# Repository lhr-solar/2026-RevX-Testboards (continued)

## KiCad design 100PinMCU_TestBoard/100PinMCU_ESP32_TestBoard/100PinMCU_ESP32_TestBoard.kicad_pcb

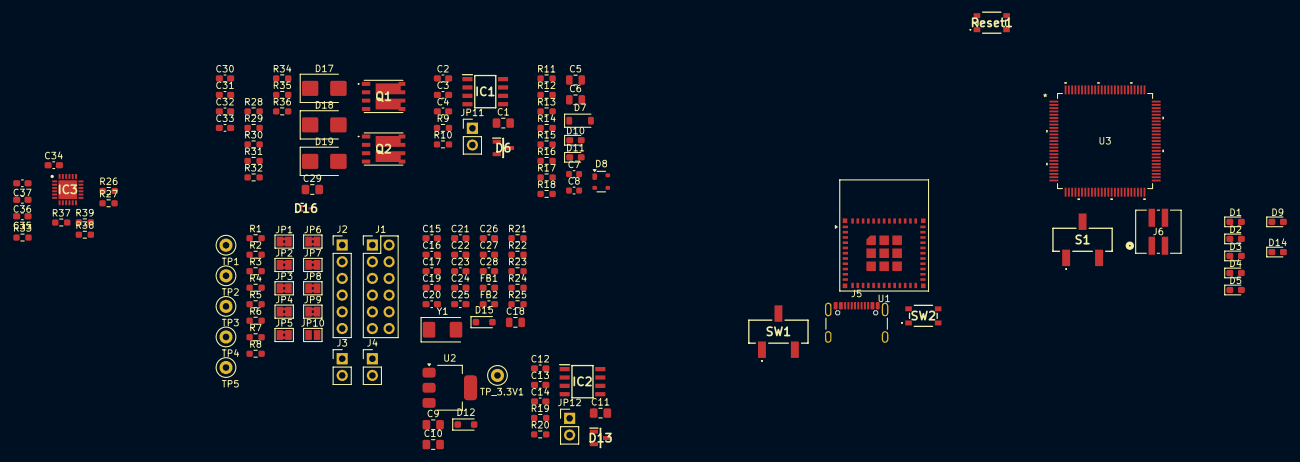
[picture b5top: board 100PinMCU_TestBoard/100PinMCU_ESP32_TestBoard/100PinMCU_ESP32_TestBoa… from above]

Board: 2 copper layers, 134 parts (0 on the bottom side), 98 nets, no tracks yet.

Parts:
C1, C9, C10, C11: 10u; C_0805_2012Metric_Pad1.18x1.45mm_HandSolder
C2, C3, C4, C12, C13, C14: 0.1u; C_0603_1608Metric_Pad1.08x0.95mm_HandSolder
C5, C6, C18: 10uF; C_0805_2012Metric
C7, C8: 0.1uF; C_0603_1608Metric
C15, C16: 26p; C_0603_1608Metric_Pad1.08x0.95mm_HandSolder
C17, C19, C20, C21, C22, C24, C26, C27, C28, C36, C37: 0.1uF; C_0603_1608Metric_Pad1.08x0.95mm_HandSolder
C23, C25, C30, C31, C32, C33, C34, C35: 1uF; C_0603_1608Metric_Pad1.08x0.95mm_HandSolder
C29: 10uF; C_0805_2012Metric_Pad1.18x1.45mm_HandSolder
D1, D2, D3, D4, D5, D14: LED; D_0603_1608Metric_Pad1.05x0.95mm_HandSolder
D6, D13: CDSOT23-T24CAN
D7: 1N5819HW-7-F; D_SOD-123
D8: SP0503BAHT; SOT-143
D9: ESP_PWR; D_0603_1608Metric_Pad1.05x0.95mm_HandSolder
D10: ESP_LED1; D_0603_1608Metric_Pad1.05x0.95mm_HandSolder
D11: ESP_LED2; D_0603_1608Metric_Pad1.05x0.95mm_HandSolder
D12: SBA130CH-AU_R1_000A1; D_SOD-323_HandSoldering
D15: D_TVS; D_SOD-323_HandSoldering
D16: TPD2EUSB30DRTR
D17: SMBJ24A-E3_52; D_SMB
D18, D19: SMBJ10A-E3_52; D_SMB
FB1, FB2: FerriteBead; L_0603_1608Metric_Pad1.05x0.95mm_HandSolder
IC1, IC2: TCAN3413DR
IC3: CYPD3177-24LQXQ
J1: Conn_02x06_Odd_Even; PinHeader_2x06_P2.54mm_Vertical
J2: Conn_01x06; PinHeader_1x06_P2.54mm_Vertical
J3, J4: Conn_01x02; PinHeader_1x02_P2.54mm_Vertical
J5: USB_C_Receptacle_USB2.0_16P; USB_C_Receptacle_GCT_USB4105-xx-A_16P_TopMnt_Horizontal
J6: SWD_Header_02x02; CONN04_878320406_MOL
JP1, JP2, JP3, JP4, JP5, JP6, JP7, JP8, JP9: Jumper_2_Bridged; SolderJumper-2_P1.3mm_Bridged2Bar_Pad1.0x1.5mm
JP10: Jumper_2_Open; SolderJumper-2_P1.3mm_Open_Pad1.0x1.5mm
JP11, JP12: TRM; PinHeader_1x02_P2.54mm_Vertical
Q1, Q2: SI7997DP-T1-GE3
R1, R2, R3, R4, R7, R8, R16, R17, R18, R25, R28, R29, R34: 1k; R_0603_1608Metric_Pad0.98x0.95mm_HandSolder
R5, R6, R37: 4.7k; R_0603_1608Metric_Pad0.98x0.95mm_HandSolder
R9, R10, R19, R20: 60; R_0603_1608Metric_Pad0.98x0.95mm_HandSolder
R11, R12, R26, R27, R32, R33, R35: 5.1k; R_0603_1608Metric_Pad0.98x0.95mm_HandSolder
R13, R14, R15, R23, R24, R30: 10k; R_0603_1608Metric_Pad0.98x0.95mm_HandSolder
R21, R22: 22; R_0603_1608Metric_Pad0.98x0.95mm_HandSolder
R31, R36: 49.9k; R_0603_1608Metric_Pad0.98x0.95mm_HandSolder
R38, R39: 2.2k; R_0603_1608Metric_Pad0.98x0.95mm_HandSolder
Reset1: Reset; TL3365AF180QG
S1: 450406020024
SW1: BOOT Switch; 450406020024
SW2: RESET Button; TL3365AF180QG
TP1, TP2, TP3, TP4, TP5: TestPoint; TestPoint_Loop_D1.80mm_Drill1.0mm_Beaded
TP_3.3V1: 3.3V; TestPoint_Loop_D1.80mm_Drill1.0mm_Beaded
U1: ESP32-C6-MINI-1
U2: MCP1826S; SOT-223-3_TabPin2
U3: STM32G491VET6; LQFP_491VET6_STM
Y1: Crystal; Crystal_SMD_Abracon_ABM3-2Pin_5.0x3.2mm

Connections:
+3.3V: C1.1, C2.1, C3.1, C11.1, C12.1, C13.1, IC1.3 (VCC), IC1.5 (SHDNV_IO), IC2.3 (VCC), IC2.5 (SHDNV_IO), JP4.2 (B), JP9.1 (A), JP10.1 (A), R5.1, R6.2, R8.1, TP1.1, TP5.1
+3.3V_ESP: C6.1, C6.2, C7.1, C7.2, JP9.2 (B), R14.1, R15.2, R16.1, SW1.1 (A), U1.3 (3V3)
/100PinMCU/3V3: C18.1, C20.1, C22.1, C24.1, C26.1, C27.1, FB2.1, J6.1, JP4.1 (A), R23.2, S1.3 (C), U3.6 (VBAT), U3.24 (VDD), U3.49 (VDD), U3.64 (VDD), U3.75 (VDD), U3.100 (VDD)
/100PinMCU/BOOT: JP1.1 (A), R24.1, U3.95 (PB8-BOOT0)
/100PinMCU/GNDA: C19.2, C21.2, C23.2, C25.2, C28.2, FB1.2, J2.6, U3.35 (VSSA)
/100PinMCU/PA9: JP6.1 (A), U3.70 (PA9)
/100PinMCU/PA10: JP7.1 (A), U3.71 (PA10)
/100PinMCU/PB12: IC2.4 (RXD), U3.51 (PB12)
/100PinMCU/PB13: IC2.1 (TXD), U3.52 (PB13)
/100PinMCU/PC0: JP2.1 (A), U3.15 (PC0)
/100PinMCU/PC1: JP3.1 (A), U3.16 (PC1)
/100PinMCU/PD2: JP5.1 (A), U3.84 (PD2)
/100PinMCU/PE8: R1.1, U3.39 (PE8)
/100PinMCU/PE11: R2.1, U3.42 (PE11)
/100PinMCU/PE12: R3.1, U3.43 (PE12)
/100PinMCU/PE14: R4.1, U3.45 (PE14)
/100PinMCU/PG10-NRST: C17.1, JP8.1 (A), R23.1, Reset1.1, U3.14 (PG10-NRST)
/100PinMCU/SWCLK: R21.1, U3.77 (PA14)
/100PinMCU/SWDIO: R22.1, U3.76 (PA13)
/100PinMCU/USB_DM: D16.2 (D-), U3.72 (PA11)
/100PinMCU/USB_DP: D16.1 (D+), U3.73 (PA12)
/100PinMCU/VDDA: C19.1, C21.1, C23.1, C25.1, C28.1, FB2.2, J2.1, U3.36 (VREF+), U3.37 (VDDA)
/ADC3_IN1: J2.2, U3.33 (PB1)
/ADC3_IN2: J2.3, U3.40 (PE9)
/ADC3_IN3: J2.4, U3.44 (PE13)
/ADC3_IN4: J2.5, U3.38 (PE7)
/CAN_Transceiver1/CAN_H: D13.1 (CAN_H), IC2.7 (CANH), J4.1, R19.1
/CAN_Transceiver1/CAN_L: D13.2 (CAN_L), IC2.6 (CANL), J4.2, JP12.2 (B)
/CAN_Transceiver/CAN_H: D6.1 (CAN_H), IC1.7 (CANH), J3.1, R9.1
/CAN_Transceiver/CAN_L: D6.2 (CAN_L), IC1.6 (CANL), J3.2, JP11.2 (B)
/ESP32/+5V_LDO_IN: C5.1, C33.1, D7.1 (K), D12.2 (A), Q2.5 (D2), Q2.6 (D2), Q2.10 (D2), Q2.12 (D2)
/ESP32/BOOT: R13.1, U1.23 (GPIO9)
/ESP32/ESP_GPIO1: JP8.2 (B), U1.19 (GPIO14)
/ESP32/ESP_GPIO2: JP1.2 (B), U1.20 (GPIO15)
/ESP32/ESP_GPIO3: JP2.2 (B), U1.24 (GPIO18)
/ESP32/ESP_GPIO4: JP3.2 (B), U1.25 (GPIO19)
/ESP32/ESP_RESET: C8.1, R7.2, R14.2, SW2.1, U1.8 (EN/CHIP_PU)
/ESP32/ESP_UART_RX: JP7.2 (B), TP3.1, U1.31 (U0TXD/GPIO16)
/ESP32/ESP_UART_TX: JP6.2 (B), TP2.1, U1.30 (U0RXD/GPIO17)
/ESP32/LED1: R17.1, U1.26 (GPIO20)
/ESP32/LED2: R18.1, U1.27 (GPIO21)
/ESP32/USB_D+: D8.2 (K), J5.A6 (D+), J5.B6 (D+), U1.18 (GPIO13/USB_D+)
/ESP32/USB_D-: D8.3 (K), J5.A7 (D-), J5.B7 (D-), U1.17 (GPIO12/USB_D-)
/ESP32/VBUSB: D7.2 (A), D8.4 (K), J5.A4 (VBUS), J5.A9 (VBUS), J5.B4 (VBUS), J5.B9 (VBUS)
/FDCAN1_RX: IC1.4 (RXD), J1.6, U3.82 (PD0)
/FDCAN1_TX: IC1.1 (TXD), J1.5, U3.83 (PD1)
/GPIO1: J1.11, U3.31 (PC5)
/I2C2_SCL: J1.2, R6.1, U3.30 (PC4)
/I2C2_SDA: J1.1, R5.2, U3.69 (PA8)
/LDO/Vout: C10.2, JP10.2 (B), TP_3.3V1.1, U2.3 (VO)
/SPI1_MISO: J1.8, U3.28 (PA6)
/SPI1_MOSI: J1.7, U3.29 (PA7)
/SPI1_NSS: J1.10, U3.26 (PA4)
/SPI1_SCK: J1.9, U3.27 (PA5)
/UART_RX: J1.4, U3.80 (PC11)
/UART_TX: J1.3, U3.79 (PC10)
/USB_PD/CC1: IC3.15 (CC1), R26.1
/USB_PD/CC2: IC3.14 (CC2), R27.1
/USB_PD/ISINK_COARSE: IC3.5 (ISNK_COARSE), R33.2, R35.1
/USB_PD/SAFE_PWR_EN: IC3.4 (SAFE_PWR_EN), R29.2
/USB_PD/SCL: IC3.13 (HPI_SCL), R38.2
/USB_PD/SDA: IC3.12 (HPI_SDA), R39.2
/USB_PD/VBUS_FET_EN: IC3.3 (VBUS_FET_EN), R28.2
/USB_PD/VBUS_MIN: IC3.1 (VBUS_MIN), R32.2, R34.1
/USB_PD/VDC_OUT: C32.1, IC3.11 (VDC_OUT), Q1.5 (D2), Q1.6 (D2), Q1.10 (D2), Q1.12 (D2)
GND: C1.2, C2.2, C3.2, C4.1, C5.2, C8.2, C9.1, C10.1, C11.2, C12.2, C13.2, C14.1, C15.1, C16.1, C17.2, C18.2, C20.2, C22.2, C24.2, C26.2, C27.2, C29.2, C34.1, C35.2, C36.2, C37.2, D1.1 (K), D2.1 (K), D3.1 (K), D4.1 (K), D5.1 (K), D6.3 (GND), D8.1 (A), D9.1 (K), D10.1 (K), D11.1 (K), D13.3 (GND), D15.1 (A1), D16.3 (GND), D17.2 (A), FB1.1, IC1.2 (GND), IC1.8 (STB), IC2.2 (GND), IC2.8 (STB), IC3.6 (ISNK_FINE), IC3.19 (GND_1), IC3.22 (GND_2), IC3.25 (GND_3), J1.12, J5.A1 (GND), J5.A12 (GND), J5.B1 (GND), J5.B12 (GND), J5.S1 (SHIELD), J5.S2 (Shield), J5.S3 (Shield), J5.S4 (Shield), J6.2, R11.2, R12.2, R25.2, R26.2, R27.2, R34.2, R35.2, Reset1.2, S1.1 (A), SW1.3 (C), SW2.2, TP4.1, U1.1 (GND), U1.2 (GND), U1.11 (GND), U1.14 (GND), U1.36 (GND), U1.37 (GND), U1.38 (GND), U1.39 (GND), U1.40 (GND), U1.41 (GND), U1.42 (GND), U1.43 (GND), U1.44 (GND), U1.45 (GND), U1.46 (GND), U1.47 (GND), U1.48 (GND), U1.49 (GND), U1.50 (GND), U1.51 (GND), U1.52 (GND), U1.53 (GND), U2.2 (GND), U3.23 (VSS), U3.48 (VSS), U3.63 (VSS), U3.74 (VSS), U3.99 (VSS)
unnamed: C4.2, R9.2, R10.1
unnamed: C14.2, R19.2, R20.1
unnamed: D1.2 (A), R1.2
unnamed: D2.2 (A), R2.2
unnamed: D3.2 (A), R3.2
unnamed: D4.2 (A), R4.2
unnamed: D5.2 (A), R8.2
unnamed: D9.2 (A), R16.2
unnamed: D10.2 (A), R17.2
unnamed: D11.2 (A), R18.2
unnamed: C9.2, D12.1 (K), U2.1 (VI)
unnamed: D14.2 (A), D15.2 (A2), R24.2, S1.2 (B)
unnamed: D14.1 (K), R25.1
unnamed: C31.2, C33.2, D18.2 (A), Q2.2 (G1), Q2.4 (G2), R29.1, R31.1
unnamed: D18.1 (K), Q2.1 (S1), Q2.3 (S2)
unnamed: C30.2, C32.2, D19.2 (A), Q1.2 (G1), Q1.4 (G2), R28.1, R30.1, R36.1
unnamed: D19.1 (K), Q1.1 (S1), Q1.3 (S2), R36.2
unnamed: IC3.10 (FLIP), R37.2
unnamed: C34.2, IC3.24 (VCCD)
unnamed: J5.A5 (CC1), R11.1
unnamed: J5.B5 (CC2), R12.1
unnamed: J6.3, R21.2
unnamed: J6.4, R22.2
unnamed: JP5.2 (B), R7.1
unnamed: JP11.1 (A), R10.2
unnamed: JP12.1 (A), R20.2
unnamed: R13.2, SW1.2 (B)
unnamed: R15.1, U1.22 (GPIO8)
unnamed: C16.2, U3.12 (PF0-OSC_IN), Y1.2
unnamed: C15.2, U3.13 (PF1-OSC_OUT), Y1.1
PD_3V3: C35.1, C36.1, C37.1, IC3.2 (VBUS_MAX), IC3.23 (VDDD), R32.1, R33.1, R37.1, R38.1, R39.1
VBUS_IN: C29.1, C30.1, C31.1, D17.1 (K), IC3.18 (VBUS_IN), Q1.7 (D1), Q1.8 (D1), Q1.9 (D1), Q1.11 (D1), Q2.7 (D1), Q2.8 (D1), Q2.9 (D1), Q2.11 (D1), R30.2, R31.2

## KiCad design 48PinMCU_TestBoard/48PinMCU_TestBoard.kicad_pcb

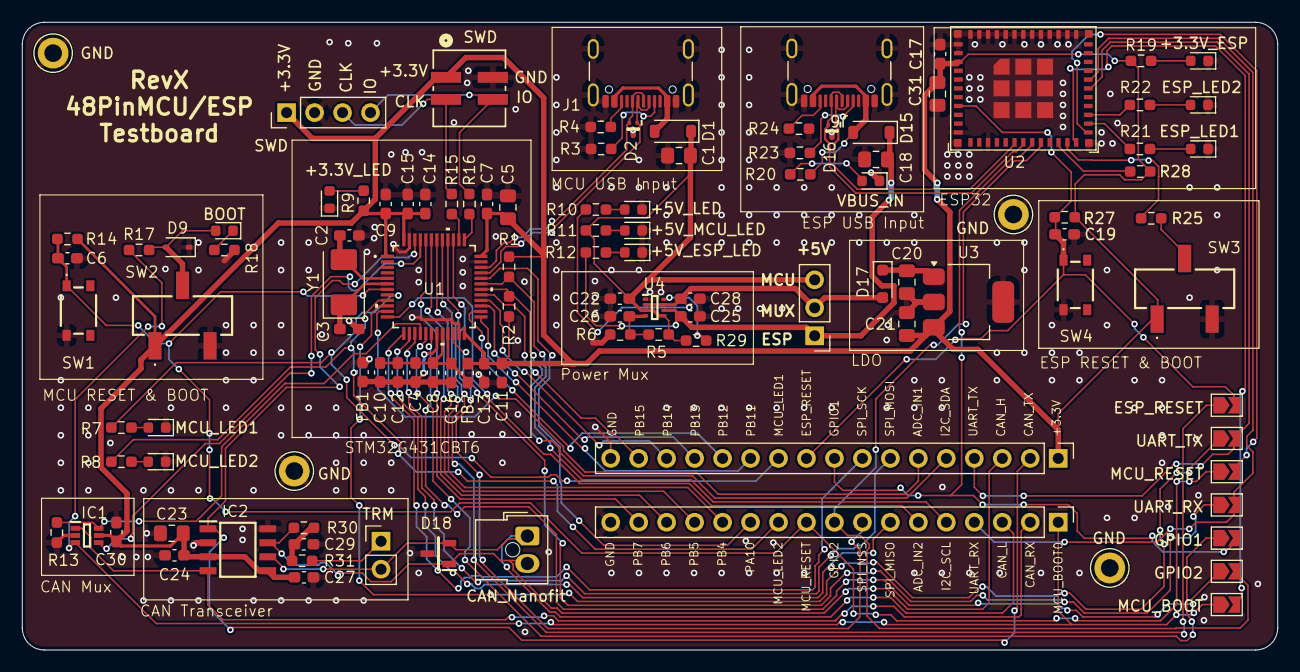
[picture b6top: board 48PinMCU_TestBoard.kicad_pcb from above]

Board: 2 copper layers, 114.0 x 57.0 mm, 112 parts (0 on the bottom side), 85 nets.

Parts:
C1, C5, C18, C31: 10uF; C_0805_2012Metric_Pad1.18x1.45mm_HandSolder
C2, C3: 26p; C_0603_1608Metric_Pad1.08x0.95mm_HandSolder
C4, C6, C7, C8, C9, C11, C13, C14, C15, C17, C19, C22, C25, C26, C28, C30: 0.1uF; C_0603_1608Metric_Pad1.08x0.95mm_HandSolder
C10, C12: 1uF; C_0603_1608Metric_Pad1.08x0.95mm_HandSolder
C16: 100nF; C_0603_1608Metric_Pad1.08x0.95mm_HandSolder
C20, C21, C23: 10u; C_0805_2012Metric_Pad1.18x1.45mm_HandSolder
C24, C27, C29: 0.1u; C_0603_1608Metric_Pad1.08x0.95mm_HandSolder
D1, D15: 1N5819HW-7-F; D_SOD-123
D2, D16: TPD2EUSB30DRTR
D3: MCU_LED1; D_0603_1608Metric
D4: MCU_LED2; D_0603_1608Metric
D5: +3.3V_LED; D_0603_1608Metric
D6: +5V_LED; D_0603_1608Metric
D7: +5V_MCU_LED; D_0603_1608Metric
D8: +5V_ESP_LED; D_0603_1608Metric
D9: D_TVS; D_SOD-323
D10: BOOT; D_0603_1608Metric
D11: +3.3V_ESP; D_0603_1608Metric
D12: VBUS_IN; D_0603_1608Metric
D13: ESP_LED1; D_0603_1608Metric
D14: ESP_LED2; D_0603_1608Metric
D17: SBA130CH-AU_R1_000A1; D_SOD-323_HandSoldering
D18: CDSOT23-T24CAN
FB1, FB2: FerriteBead; C_0603_1608Metric_Pad1.08x0.95mm_HandSolder
IC1: 74LVC1G157GW,125; SOP65P210X110-6N
IC2: TCAN3413DR
J1, J6: USB_C_Receptacle_USB2.0_16P; USB_C_Receptacle_GCT_USB4105-xx-A_16P_TopMnt_Horizontal
J2: CAN_Nanofit; Molex_Nano-Fit_105309-xx02_1x02_P2.50mm_Vertical
J3: Conn_01x03; PinHeader_1x03_P2.54mm_Vertical
J4: SWD; PinHeader_1x04_P2.54mm_Vertical
J5: SWD; CONN04_878320406_MOL
J7, J8: Conn_01x17; PinHeader_1x17_P2.54mm_Vertical
JP8: ESP_RESET; SolderJumper-2_P1.3mm_Open_TrianglePad1.0x1.5mm
JP9: UART_TX; SolderJumper-2_P1.3mm_Open_TrianglePad1.0x1.5mm
JP10: UART_RX; SolderJumper-2_P1.3mm_Open_TrianglePad1.0x1.5mm
JP11: GPIO1; SolderJumper-2_P1.3mm_Open_TrianglePad1.0x1.5mm
JP12: GPIO2; SolderJumper-2_P1.3mm_Open_TrianglePad1.0x1.5mm
JP13: MCU_BOOT; SolderJumper-2_P1.3mm_Open_TrianglePad1.0x1.5mm
JP14: MCU_RESET; SolderJumper-2_P1.3mm_Open_TrianglePad1.0x1.5mm
JP15: TRM; PinHeader_1x02_P2.54mm_Vertical
R1, R2, R13, R14, R17, R25, R27, R28, R29: 10k; R_0603_1608Metric_Pad0.98x0.95mm_HandSolder
R3, R4, R23, R24: 5.1k; R_0603_1608Metric_Pad0.98x0.95mm_HandSolder
R5: 16k; R_0603_1608Metric_Pad0.98x0.95mm_HandSolder
R6: 4.7k; R_0603_1608Metric_Pad0.98x0.95mm_HandSolder
R7, R8, R9, R18, R19, R21, R22: 1k; R_0603_1608Metric_Pad0.98x0.95mm_HandSolder
R10, R11, R12, R20: 2.2k; R_0603_1608Metric_Pad0.98x0.95mm_HandSolder
R15, R16: 22; R_0603_1608Metric_Pad0.98x0.95mm_HandSolder
R30, R31: 60; R_0603_1608Metric_Pad0.98x0.95mm_HandSolder
SW1: Reset; TL3365AF180QG
SW2: SW_SPDT; BootSW
SW3: BOOT Switch; BootSW
SW4: RESET Button; TL3365AF180QG
TP1, TP2, TP3, TP4: GND; TestPoint_Keystone_5005-5009_Compact
U1: STM32G431CBT6; 48PinMCU
U2: ESP32-C6-MINI-1
U3: MCP1826S; SOT-223-3_TabPin2
U4: TPS2117DRLR; SOTFL50P160X60-8N
Y1: Crystal; Crystal_SMD_Abracon_ABM3-2Pin_5.0x3.2mm

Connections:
+3.3V: C5.1, C7.1, C9.1, C11.1, C13.1, C14.1, C15.1, C17.1, C21.2, C23.1, C24.1, C27.1, C30.1, C31.1, FB2.1, IC1.5 (VCC), IC2.3 (VCC), IC2.5 (SHDNV_IO), J4.1, J5.1, J7.1, R1.1, R2.1, R9.1, R14.2, R19.1, R27.1, R28.2, SW2.1 (A), SW3.1 (A), U1.1 (VBAT), U1.24 (VDD), U1.36 (VDD), U1.48 (VDD), U2.3 (3V3), U3.3 (VO)
+5V: C28.1, D17.2 (A), J3.2, R10.1, U4.2 (VOUT), U4.7 (VOUT__1)
+5V_ESP: C18.1, C25.1, D15.1 (K), J3.1, R12.1, U4.6 (VIN2)
+5V_MCU: C1.1, C22.1, D1.1 (K), J3.3, R5.1, R11.1, R29.1, U4.3 (VIN1), U4.5 (MODE)
/ADC_IN_1: J7.6, U1.11 (PA3)
/ADC_IN_2: J8.6, U1.12 (PA4)
/CAN_H: D18.1 (CAN_H), IC2.7 (CANH), J2.2, J7.3, R30.1
/CAN_L: D18.2 (CAN_L), IC2.6 (CANL), J2.1, J8.3, JP15.2 (B)
/CAN_RX: IC1.1 (I1), IC2.4 (RXD), J8.2
/CAN_TX: IC2.1 (TXD), J7.2, U1.46 (PB9)
/ESP32/BOOT: R25.1, U2.23 (GPIO9)
/ESP32/LED1: R21.1, U2.26 (GPIO20)
/ESP32/LED2: R22.1, U2.27 (GPIO21)
/ESP32/USB_D+: D16.2 (D-), J6.A6 (D+), J6.B6 (D+), U2.18 (GPIO13/USB_D+)
/ESP32/USB_D-: D16.1 (D+), J6.A7 (D-), J6.B7 (D-), U2.17 (GPIO12/USB_D-)
/ESP32/VBUS: D15.2 (A), J6.A4 (VBUS), J6.A9 (VBUS), J6.B4 (VBUS), J6.B9 (VBUS), R20.1
/ESP_BREAKOUT1_E: J7.9, JP11.2 (B), U2.19 (GPIO14)
/ESP_BREAKOUT1_M: JP11.1 (A), U1.17 (PB1)
/ESP_BREAKOUT2_E: J8.9, JP12.2 (B), U2.20 (GPIO15)
/ESP_BREAKOUT2_M: JP12.1 (A), U1.18 (PB2)
/ESP_RESET_E: C19.1, J7.10, JP8.2 (B), R27.2, SW4.1, U2.8 (EN/CHIP_PU)
/ESP_RESET_M: JP8.1 (A), U1.40 (PB3)
/ESP_UART_RX_E: J8.4, JP10.2 (B), U2.31 (U0TXD/GPIO16)
/ESP_UART_RX_M: JP10.1 (A), U1.22 (PB10)
/ESP_UART_TX_E: J7.4, JP9.2 (B), U2.30 (U0RXD/GPIO17)
/ESP_UART_TX_M: JP9.1 (A), U1.10 (PA2)
/I2C_SCL: J8.5, R1.2, U1.31 (PA9)
/I2C_SDA: J7.5, R2.2, U1.30 (PA8)
/MCU/CAN_EN: IC1.6 (S), R13.2, U1.16 (PB0)
/MCU/CAN_RX/BOOT0: IC1.4 (Y), U1.45 (PB8-BOOT0)
/MCU/GNDA: C4.2, C8.2, C10.2, C12.2, C16.2, FB1.1, U1.19 (VSSA)
/MCU/SWCLK: R15.1, U1.38 (PA14)
/MCU/SWDIO: R16.1, U1.37 (PA13)
/MCU/VDDA: C4.1, C8.1, C10.1, C12.1, C16.1, FB2.2, U1.20 (VREF+), U1.21 (VDDA)
/MCU_BOOT0_E: JP13.2 (B), U2.24 (GPIO18)
/MCU_BOOT0_M: IC1.3 (I0), J8.1, JP13.1 (A), R17.1
/MCU_LED_1: J7.11, R7.1, U1.8 (PA0)
/MCU_LED_2: J8.11, R8.1, U1.9 (PA1)
/MCU_RESET_E: JP14.2 (B), U2.25 (GPIO19)
/MCU_RESET_M: C6.1, J8.10, JP14.1 (A), R14.1, SW1.1, U1.7 (PG10-NRST)
/PA10: J8.12, U1.32 (PA10)
/PB4: J8.13, U1.41 (PB4)
/PB5: J8.14, U1.42 (PB5)
/PB6: J8.15, U1.43 (PB6)
/PB7: J8.16, U1.44 (PB7)
/PB11: J7.12, U1.25 (PB11)
/PB12: J7.13, U1.26 (PB12)
/PB13: J7.14, U1.27 (PB13)
/PB14: J7.15, U1.28 (PB14)
/PB15: J7.16, U1.29 (PB15)
/Power Mux/PR1: C26.1, R5.2, R6.1, U4.4 (PR1)
/SPI_MISO: J8.7, U1.14 (PA6)
/SPI_MOSI: J7.7, U1.15 (PA7)
/SPI_NSS: J8.8, U1.39 (PA15)
/SPI_SCK: J7.8, U1.13 (PA5)
/USB_D+: D2.2 (D-), J1.A6 (D+), J1.B6 (D+), U1.34 (PA12)
/USB_D-: D2.1 (D+), J1.A7 (D-), J1.B7 (D-), U1.33 (PA11)
/VBUS: D1.2 (A), J1.A4 (VBUS), J1.A9 (VBUS), J1.B4 (VBUS), J1.B9 (VBUS)
GND: C1.2, C2.2, C3.1, C5.2, C6.2, C7.2, C9.2, C11.2, C13.2, C14.2, C15.2, C17.2, C18.2, C19.2, C20.1, C21.1, C22.2, C23.2, C24.2, C25.2, C26.2, C27.2, C28.2, C29.1, C30.2, C31.2, D2.3 (GND), D3.1 (K), D4.1 (K), D5.1 (K), D6.1 (K), D7.1 (K), D8.1 (K), D9.1 (A1), D11.1 (K), D12.1 (K), D13.1 (K), D14.1 (K), D16.3 (GND), D18.3 (GND), FB1.2, IC1.2 (GND), IC2.2 (GND), IC2.8 (STB), J1.A1 (GND), J1.A12 (GND), J1.B1 (GND), J1.B12 (GND), J1.S1 (SHIELD), J1.S2 (Shield), J1.S3 (Shield), J1.S4 (Shield), J4.2, J5.2, J6.A1 (GND), J6.A12 (GND), J6.B1 (GND), J6.B12 (GND), J6.S1 (SHIELD), J6.S2 (Shield), J6.S3 (Shield), J6.S4 (Shield), J7.17, J8.17, R3.2, R4.2, R6.2, R13.1, R18.2, R23.2, R24.2, SW1.2, SW2.3 (C), SW3.3 (C), SW4.2, TP1.1, TP2.1, TP3.1, TP4.1, U1.23 (VSS), U1.35 (VSS), U1.47 (VSS), U2.1 (GND), U2.2 (GND), U2.11 (GND), U2.14 (GND), U2.36 (GND), U2.37 (GND), U2.38 (GND), U2.39 (GND), U2.40 (GND), U2.41 (GND), U2.42 (GND), U2.43 (GND), U2.44 (GND), U2.45 (GND), U2.46 (GND), U2.47 (GND), U2.48 (GND), U2.49 (GND), U2.50 (GND), U2.51 (GND), U2.52 (GND), U2.53 (GND), U3.2 (GND), U4.1 (GND)
unnamed: C29.2, R30.2, R31.1
unnamed: D3.2 (A), R7.2
unnamed: D4.2 (A), R8.2
unnamed: D5.2 (A), R9.2
unnamed: D6.2 (A), R10.2
unnamed: D7.2 (A), R11.2
unnamed: D8.2 (A), R12.2
unnamed: D9.2 (A2), D10.2 (A), R17.2, SW2.2 (B)
unnamed: D10.1 (K), R18.1
unnamed: D11.2 (A), R19.2
unnamed: D12.2 (A), R20.2
unnamed: D13.2 (A), R21.2
unnamed: D14.2 (A), R22.2
unnamed: C20.2, D17.1 (K), U3.1 (VI)
unnamed: J1.A5 (CC1), R3.1
unnamed: J1.B5 (CC2), R4.1
unnamed: J4.3, J5.3, R15.2
unnamed: J4.4, J5.4, R16.2
unnamed: J6.A5 (CC1), R23.1
unnamed: J6.B5 (CC2), R24.1
unnamed: JP15.1 (A), R31.2
unnamed: R25.2, SW3.2 (B)
unnamed: C2.1, U1.5 (PF0-OSC_IN), Y1.2
unnamed: C3.2, U1.6 (PF1-OSC_OUT), Y1.1
unnamed: R28.1, U2.22 (GPIO8)
unnamed: R29.2, U4.8 (ST)

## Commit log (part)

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2026-05-11 started pd + boost testboard
2026-05-13 Add project link to README
2026-05-13 some stuff
2026-05-15 schematic
2026-05-15 init
2026-05-15 initial review
2026-05-15 init layout
2026-05-15 updated p/n
2026-05-18 addressed comments, changed PD block a little
2026-05-18 reviewed lakshay, ready for lil shah
2026-05-18 updated relative path for footprint/design path
2026-05-18 addressed all reviews, starting layout
2026-05-19 comments, load resistors, stuff idk
2026-05-19 esp32 design block will be updated later
2026-05-19 early layout stuff
2026-05-21 more layout
2026-05-21 cooking or no??
2026-05-21 something
2026-05-21 some tweaks
2026-05-21 footprints fixed
2026-05-21 footprints fixed actually
2026-05-22 fuse holder
2026-05-23 initial commit, schematic for testboard
2026-05-23 addressed final rounds of schematic comments, inital layouting
2026-05-24 made tony changes; broke out more pins
2026-05-28 lakshay comments addressed footprint p/n in progress
2026-05-28 comments
2026-05-28 addressed reviews
2026-05-29 1st iteration layout review
2026-05-29 pre japan flight
2026-05-29 pre board
2026-05-29 fixes made
2026-05-29 more fixes
2026-05-30 during flight
2026-05-30 clean up
2026-05-30 production files
2026-05-30 changed gitignore to push bom
2026-05-30 All fixes fixed
2026-05-30 preliminary layout blocks
2026-05-30 mount fuji tmrw
2026-05-30 addressed all final comments, review?
2026-05-31 Layout
2026-05-31 finished tony's review, should be good?
2026-05-31 added p/n for missing fields
2026-05-31 ready for lil shah
2026-05-31 added shorting jumpers
2026-06-01 added bypass caps in series with ESP DC input
2026-06-01 layout tweaks
2026-06-01 temp
2026-06-01 bump shpt
2026-06-01 made more changes!!
2026-06-01 gerbers
2026-06-01 add mux
2026-06-01 save before laptop dies
2026-06-01 more
2026-06-01 okay
2026-06-01 clark
2026-06-01 separate subcircuits
2026-06-01 can layout
2026-06-01 mcu layout
2026-06-01 all subcircuits layout
2026-06-01 updated with PP + gen gebers
2026-06-01 JLC gebers + minor silk fixes
2026-06-02 schem fixes + some semblance of layout ish
2026-06-02 more layout but me go sleep now
2026-06-03 she's an onion now
2026-06-03 initial layout (yes I will add funny silkscreen tmrw)
2026-06-03 oops my edge cuts were weird
2026-06-04 updated with new comments + new gen gebers
2026-06-05 ravi comments addressed
2026-06-05 silkscreen + gerbers
2026-06-05 almost pulled a prat
2026-06-18 fixed gitignore so bom shows up
